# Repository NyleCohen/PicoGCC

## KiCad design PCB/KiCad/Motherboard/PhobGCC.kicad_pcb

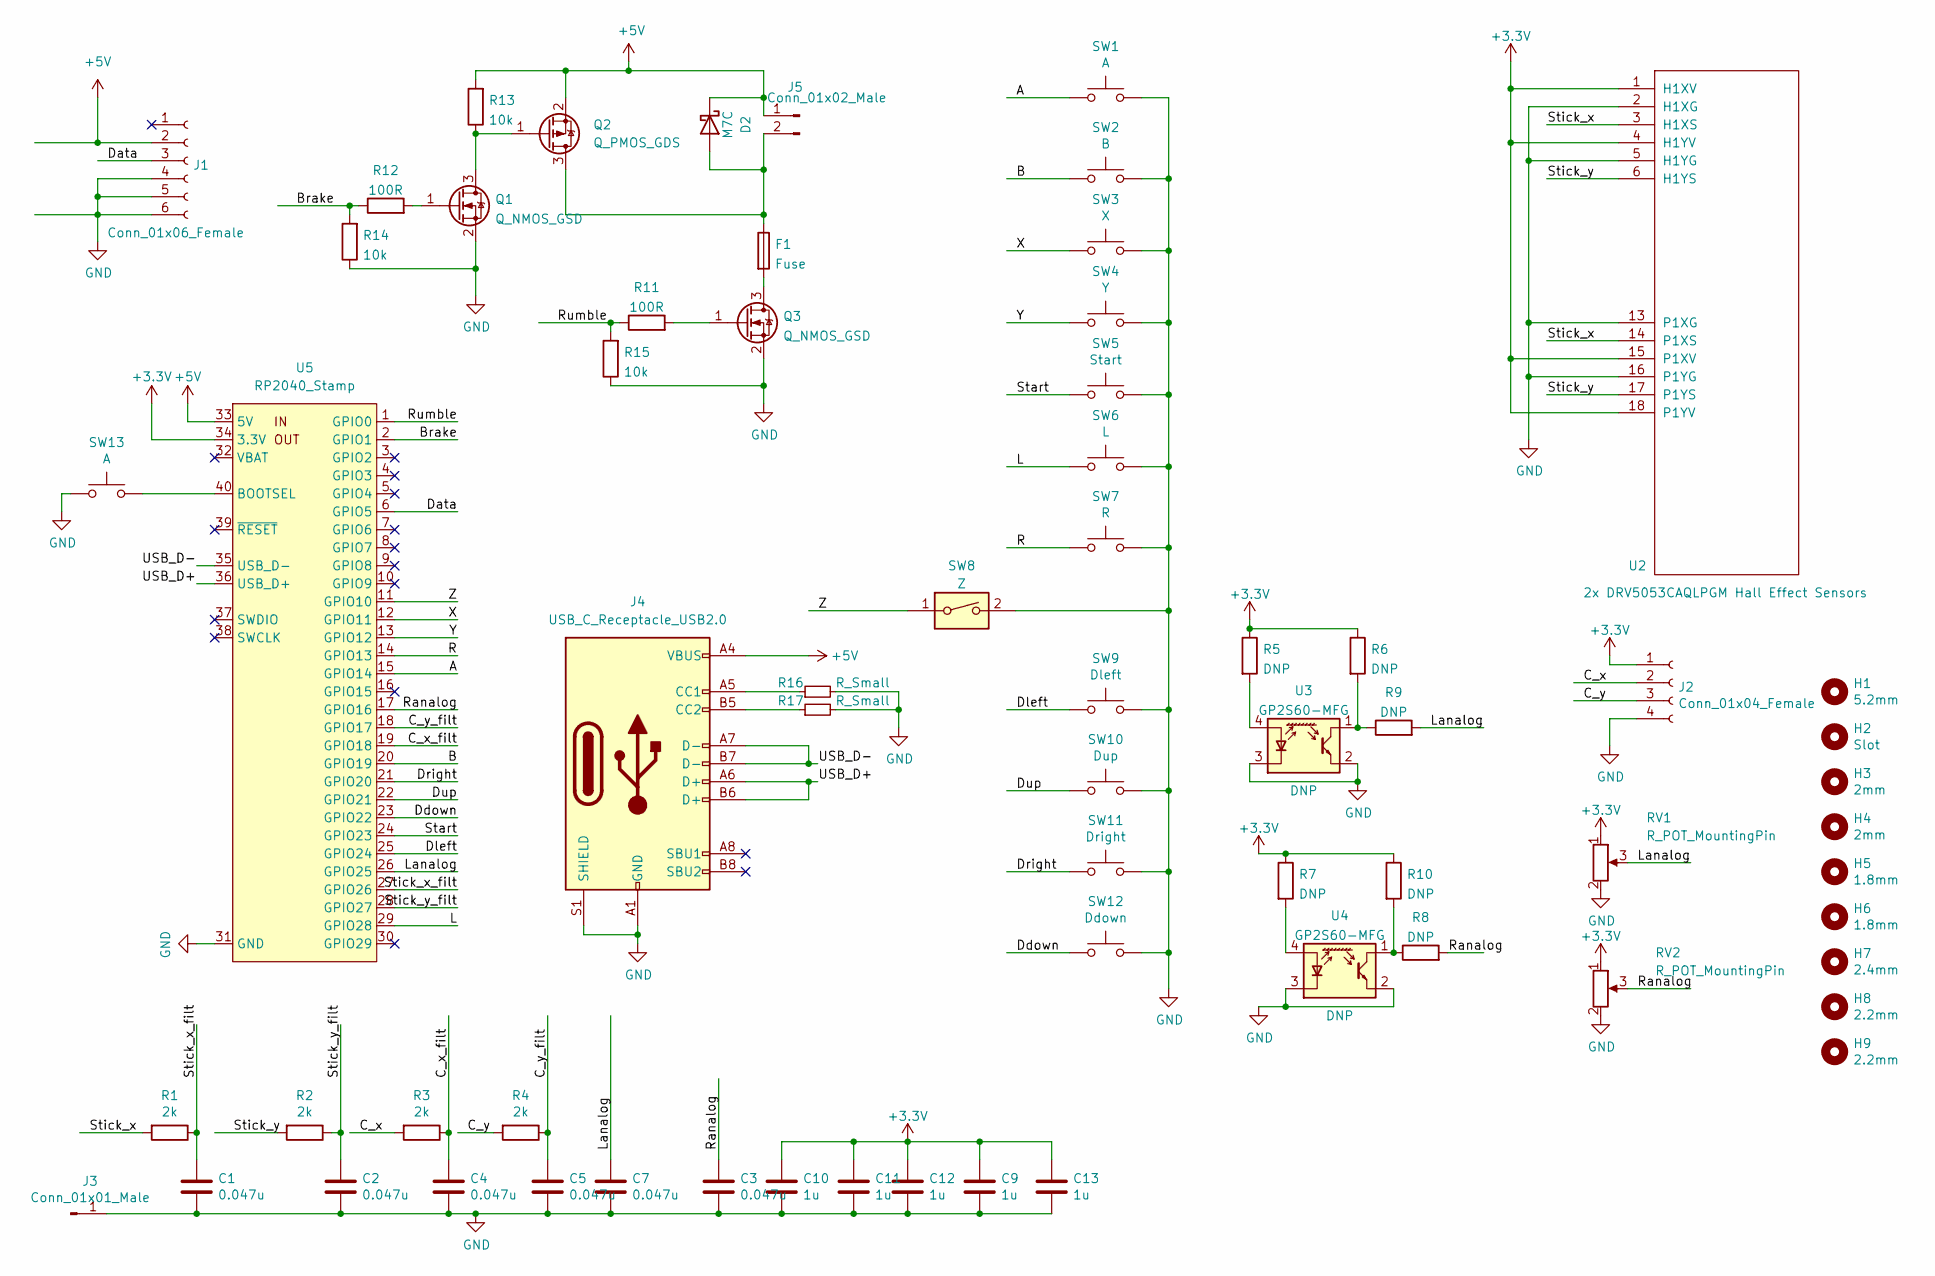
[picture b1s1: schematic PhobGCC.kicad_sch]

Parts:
C1, C2, C3, C4, C5, C7: 0.047u; C_0603_HandSoldering; LCSC C1622
C9, C10, C11, C12, C13: 1u; C_0603_1608Metric_Pad1.08x0.95mm_HandSolder; LCSC C15849
D2: M7C; D_SOD-123; LCSC C8598
F1: Fuse; Fuse_1206_3216Metric; LCSC C69680
H1: 5.2mm; MountingHole_5.2mm
H2: Slot
H3, H4: 2mm; MountingHole_2.0mm
H5, H6: 1.8mm; MountingHole_1.8mm
H7: 2.4mm; MountingHole_2.4mm
H8, H9: 2.2mm; MountingHole_2.2mm
J1: Conn_01x06_Female; GCC_Header_Straight_1x06_Pitch2.00mm
J2: Conn_01x04_Female; PinHeader_1x04_P2.00mm_Vertical
J3: Conn_01x01_Male; PinHeader_1x01_P2.54mm_Vertical
J4: USB_C_Receptacle_USB2.0; GCT_USB4155-03-C_REVA
J5: Conn_01x02_Male; Pin_Header_Straight_1x02_Pitch2.54mm
Q1, Q3: Q_NMOS_GSD; SOT-23; LCSC C20917
Q2: Q_PMOS_GDS; SOT-23; LCSC C15127
R1: 2k; R_0603_1608Metric_Pad0.98x0.95mm_HandSolder; Manufacturer PN 0603WAF1002T5ECopy; LCSC C22975
R2, R3, R4: 2k; R_0603_1608Metric_Pad0.98x0.95mm_HandSolder; LCSC C22975
R5, R6, R7, R8, R9, R10: DNP; R_0603_1608_DNP
R11, R12: 100R; R_0603_1608Metric_Pad0.98x0.95mm_HandSolder; LCSC C22775
R13, R14, R15: 10k; R_0603_1608Metric_Pad0.98x0.95mm_HandSolder; LCSC C25804
R16, R17: R_Small; R_0603_1608Metric_Pad0.98x0.95mm_HandSolder
RV1, RV2: R_POT_MountingPin; GCC_Slider
SW1, SW13: A; ABXY_Contact_Omron_Switch
SW2: B; ABXY_Contact_Omron_Switch
SW3: X; ABXY_Contact_Omron_Switch
SW4: Y; ABXY_Contact_Omron_Switch
SW5: Start; Start_Contact
SW6: L; Pin_Header_Straight_1x02_Pitch2.54mm
SW7: R; Pin_Header_Straight_1x02_Pitch2.54mm
SW8: Z; Z_Switch_Edge_Omron
SW9: Dleft; Dpad_Contact_TL3315NF_2
SW10: Dup; Dpad_Contact_TL3315NF_2
SW11: Dright; Dpad_Contact_TL3315NF_2
SW12: Ddown; Dpad_Contact_TL3315NF_2
U2: 2x DRV5053CAQLPGM Hall Effect Sensors; GCC_Stickbox_2
U3, U4: GP2S60-MFG; Sharp_Microelectronics-GP2S60-MFG
U5: RP2040_Stamp; RP2040_Stamp_SMD

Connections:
+3V3: C9.1, C10.1, C11.1, C12.1, C13.1, J2.1, R5.1, R6.1, R7.1, R10.1, RV1.1 (V+), RV2.1 (V+), U2.1 (H1XV), U2.4 (H1YV), U2.15 (P1XV), U2.18 (P1YV), U5.34 (3.3V)
+5V: D2.1 (K), J1.2, J4.A4 (VBUS), J4.A9 (VBUS), J4.B4 (VBUS), J4.B9 (VBUS), J5.1, Q2.2 (S), R13.2, U5.33 (5V)
/A: SW1.1, U5.15 (GPIO14)
/B: SW2.1, U5.20 (GPIO19)
/Brake: R12.1, R14.2, U5.2 (GPIO1)
/C_x: J2.2, R3.2
/C_x_filt: C4.1, R3.1, U5.19 (GPIO18)
/C_y: J2.3, R4.2
/C_y_filt: C5.1, R4.1, U5.18 (GPIO17)
/Data: J1.3, U5.6 (GPIO5)
/Ddown: SW12.1, U5.23 (GPIO22)
/Dleft: SW9.1, U5.25 (GPIO24)
/Dright: SW11.1, U5.21 (GPIO20)
/Dup: SW10.1, U5.22 (GPIO21)
/L: SW6.1, U5.29 (GPIO28)
/Lanalog: C7.1, R9.2, RV1.3 (Signal), U5.26 (GPIO25)
/R: SW7.1, U5.14 (GPIO13)
/Ranalog: C3.1, R8.2, RV2.3 (Signal), U5.17 (GPIO16)
/Rumble: R11.1, R15.2, U5.1 (GPIO0)
/Start: SW5.1, U5.24 (GPIO23)
/Stick_x: R1.2, U2.3 (H1XS), U2.14 (P1XS)
/Stick_x_filt: C1.1, R1.1, U5.27 (GPIO26)
/Stick_y: R2.2, U2.6 (H1YS), U2.17 (P1YS)
/Stick_y_filt: C2.1, R2.1, U5.28 (GPIO27)
/USB_D+: J4.A6 (D+), J4.B6 (D+), U5.36 (USB_D+)
/USB_D-: J4.A7 (D-), J4.B7 (D-), U5.35 (USB_D-)
/X: SW3.1, U5.12 (GPIO11)
/Y: SW4.1, U5.13 (GPIO12)
/Z: SW8.1, U5.11 (GPIO10)
GND: C1.2, C2.2, C3.2, C4.2, C5.2, C7.2, C9.2, C10.2, C11.2, C12.2, C13.2, J1.4, J1.5, J1.6, J2.4, J3.1, J4.A1 (GND), J4.A12 (GND), J4.B1 (GND), J4.B12 (GND), J4.S1 (SHIELD), Q1.2 (S), Q3.2 (S), R14.1, R15.1, R16.2, R17.2, RV1.2 (GND), RV2.2 (GND), SW1.2, SW2.2, SW3.2, SW4.2, SW5.2, SW6.2, SW7.2, SW8.2, SW9.2, SW10.2, SW11.2, SW12.2, SW13.1, U2.2 (H1XG), U2.5 (H1YG), U2.13 (P1XG), U2.16 (P1YG), U3.2 (E), U3.3 (K), U4.2 (E), U4.3 (K), U5.31 (GND); also elsewhere on the board
unnamed: D2.2 (A), F1.1, J5.2, Q2.3 (D)
unnamed: F1.2, Q3.3 (D)
unnamed: J4.A5 (CC1), R16.1
unnamed: J4.B5 (CC2), R17.1
unnamed: Q1.1 (G), R12.2
unnamed: Q1.3 (D), Q2.1 (G), R13.1
unnamed: Q3.1 (G), R11.2
unnamed: R5.2, U3.4 (A)
unnamed: R6.2, R9.1, U3.1 (C)
unnamed: R7.2, U4.4 (A)
unnamed: R8.1, R10.2, U4.1 (C)
unnamed: SW13.2, U5.40 (BOOTSEL)

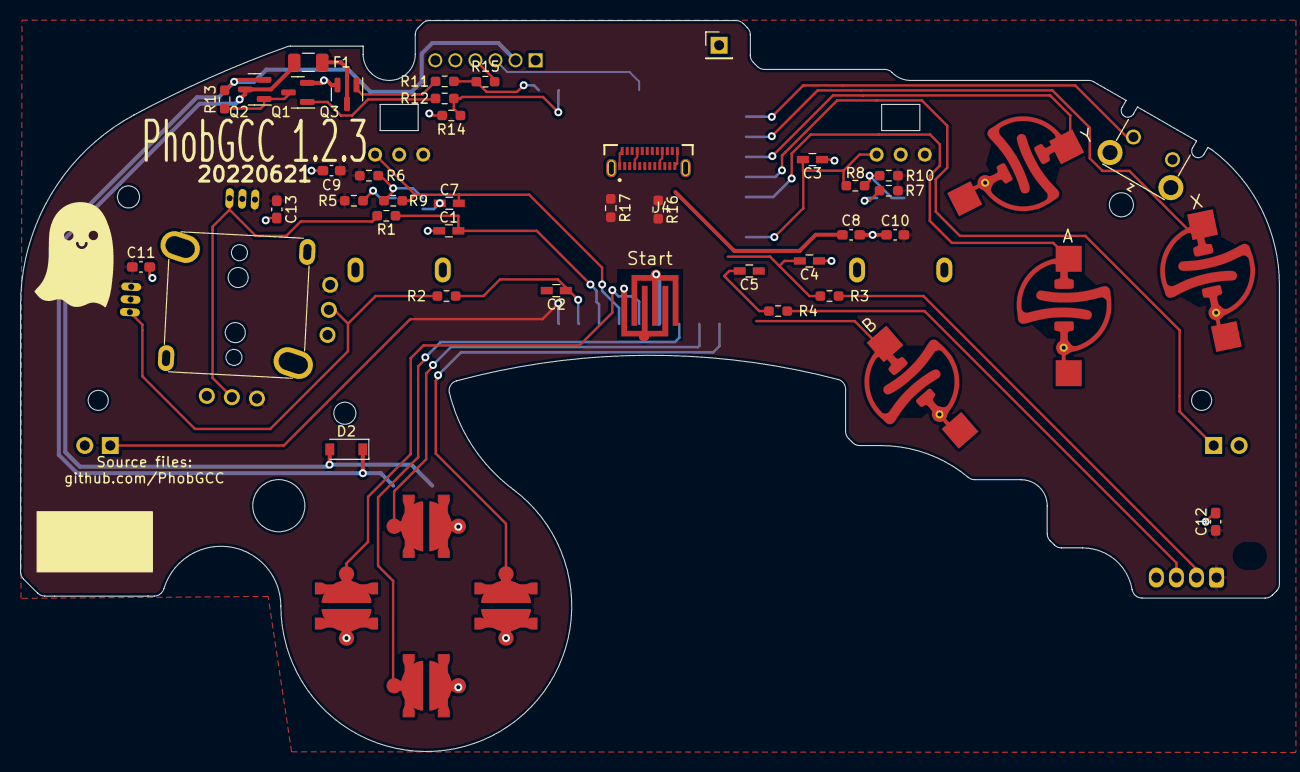
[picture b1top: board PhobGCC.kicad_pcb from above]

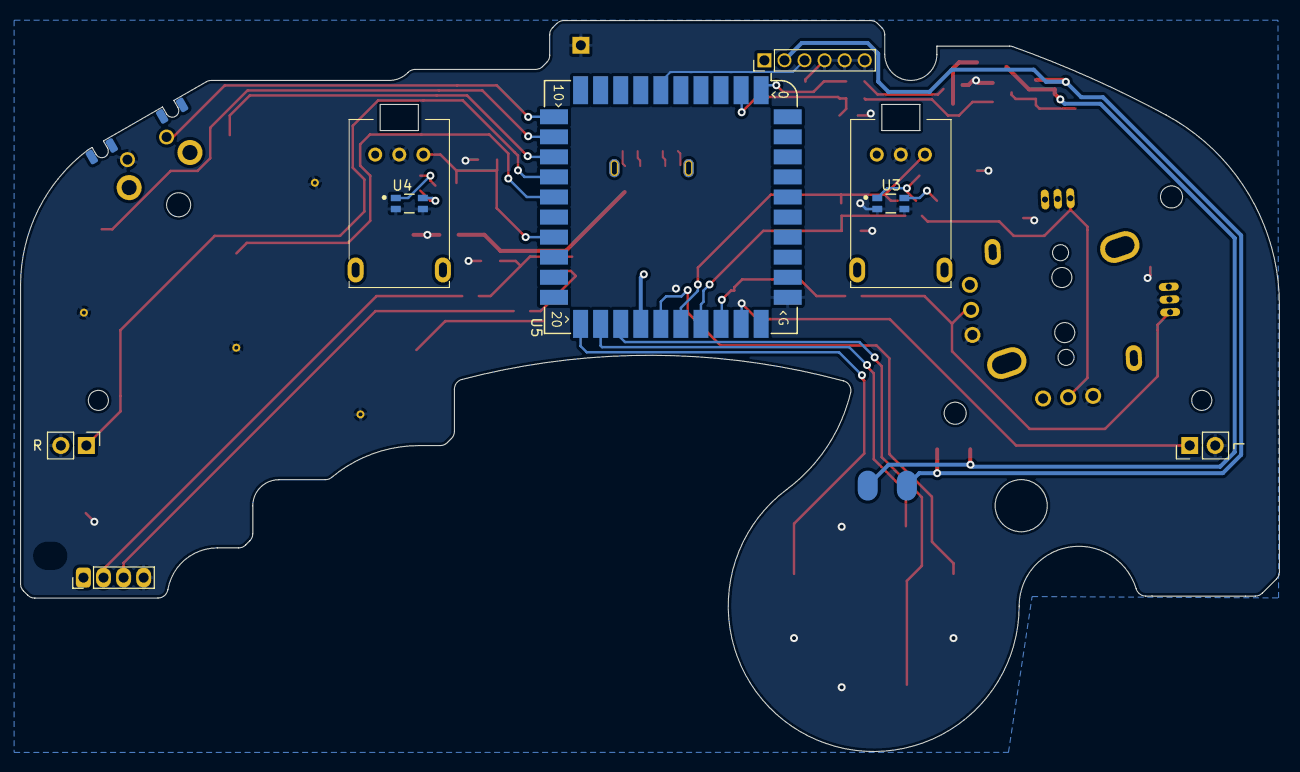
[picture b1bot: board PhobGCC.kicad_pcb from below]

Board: 2 copper layers, 125.5 x 72.9 mm, 64 parts (10 on the bottom side), 41 nets.

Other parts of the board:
C8: 1u; C_0603_1608Metric_Pad1.08x0.95mm_HandSolder

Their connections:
GND: C8.2; also elsewhere on the board

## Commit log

2022-07-14 [ImgBot] Optimize images
    *Total -- 686.99kb -> 439.14kb (36.08%)
    /PCB/Graphics/Button_layout_template.svg -- 1.81kb -> 0.27kb (85.04%)
    /PCB/Graphics/Cute Ghost.png -- 131.36kb -> 54.44kb (58.56%)
    /PCB/Graphics/Start_layout.svg -- 4.04kb -> 2.00kb (50.45%)
    /PCB/Graphics/DPad_Contact.svg -- 4.21kb -> 2.18kb (48.25%)
    /PCB/Graphics/DPad_layout.svg -- 5.05kb -> 3.04kb (39.84%)
2022-07-14 Replaced teensy 4 with pico stamp and completed basic schematic and layout changes
